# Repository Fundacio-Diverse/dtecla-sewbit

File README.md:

# sew:bit
## Una placa de expansión de código abierto que amplía las posibilidades del micro:bit para la informática textil y los dispositivos wearables en la educación primaria (K-6)
Sew:bit es una placa de expansión de código abierto para el BBC micro:bit, diseñada en el marco de un Fab Lab para facilitar la creación de dispositivos wearables y textiles electrónicos en la educación primaria (de infantil a 6.º de primaria).

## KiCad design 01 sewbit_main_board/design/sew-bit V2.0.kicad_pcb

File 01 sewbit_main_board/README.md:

## Diseño
La placa sew:bit está diseñada usando el EDA open source Kicad en su versión 8.0. En la carpeta Diseño podréis encontrar el editable del mismo, así como el svg de las serigrafía.

Para más información sobre [Kicad](https://www.kicad.org/).

## Producción
La placa se puede fabricar en cualquier casa de fabricación de pcbs, los gerber que hay en la carpeta son los requeridos por JLCPCB en su [guía para exportar archivos de producción en Kicad 8](https://jlcpcb.com/help/article/how-to-generate-gerber-and-drill-files-in-kicad-8).

El edge connector de micro:bit SMD no está disponible, al menos a fecha de Junio 2026, en la lista de partes de JLCPCB y se ha de comprar independientemente, nosotros hemos probado:

- [Sparkfun](https://www.digikey.es/es/products/detail/sparkfun-electronics/17253/13282853)
- [Aliexpress](https://es.aliexpress.com/item/1005008738053304.html?spm=a2g0o.productlist.main.2.45feaLOyaLOy7o&algo_pvid=e5b15cc3-2964-421c-8b64-d8b5d52a2186&algo_exp_id=e5b15cc3-2964-421c-8b64-d8b5d52a2186-1&pdp_ext_f=%7B%22order%22%3A%2218%22%2C%22eval%22%3A%221%22%2C%22fromPage%22%3A%22search%22%7D&pdp_npi=6%40dis%21EUR%211.01%210.88%21%21%211.14%210.99%21%40211b680e17636441302883424e213a%2112000046465521793%21sea%21ES%210%21ABX%211%210%21n_tag%3A-29910%3Bd%3A487d80f5%3Bm03_new_user%3A-29895&curPageLogUid=AhU2Qnlq59mS&utparam-url=scene%3Asearch%7Cquery_from%3A%7Cx_object_id%3A1005008738053304%7C_p_origin_prod%3A)

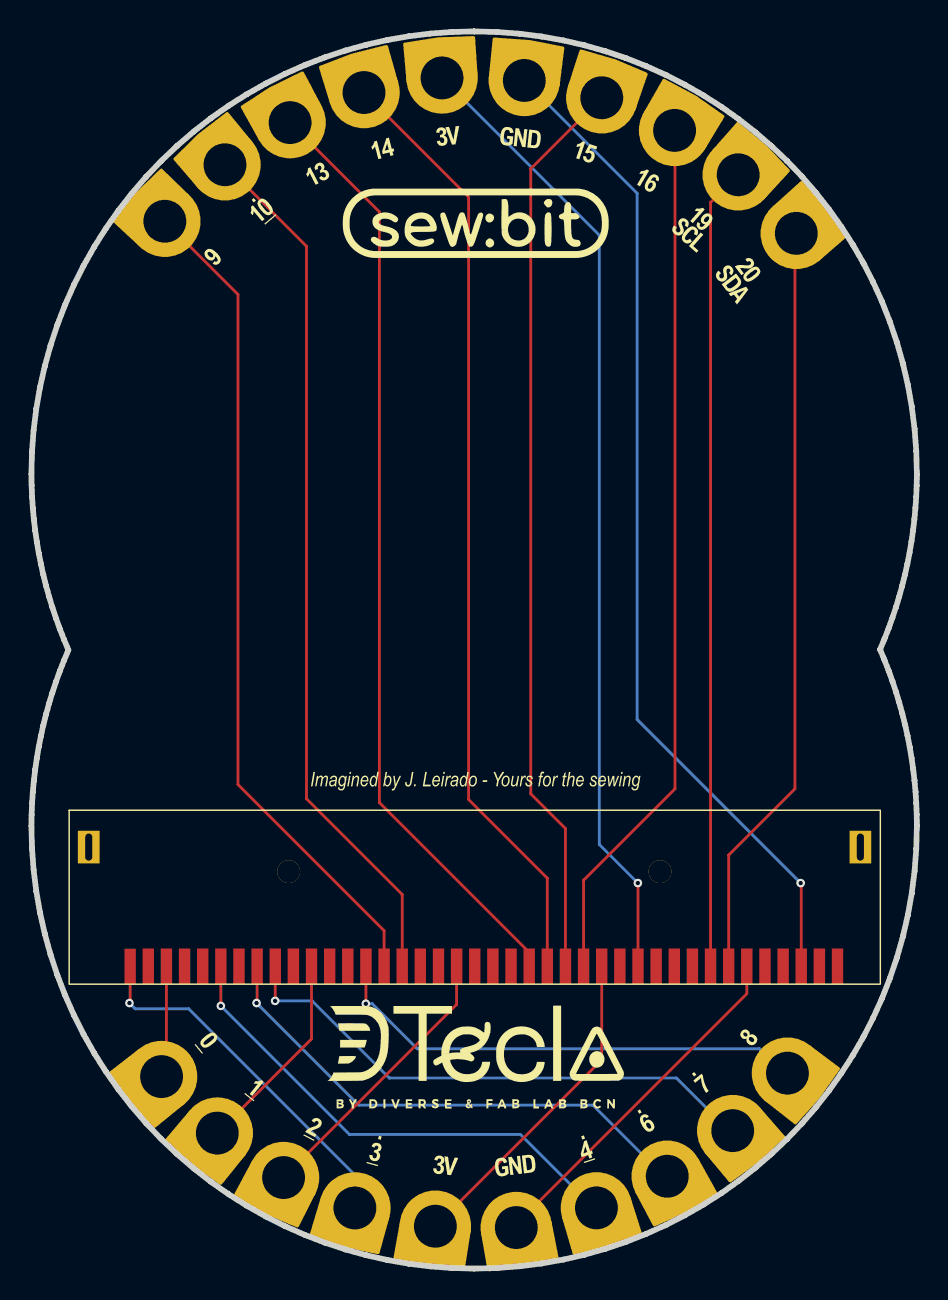
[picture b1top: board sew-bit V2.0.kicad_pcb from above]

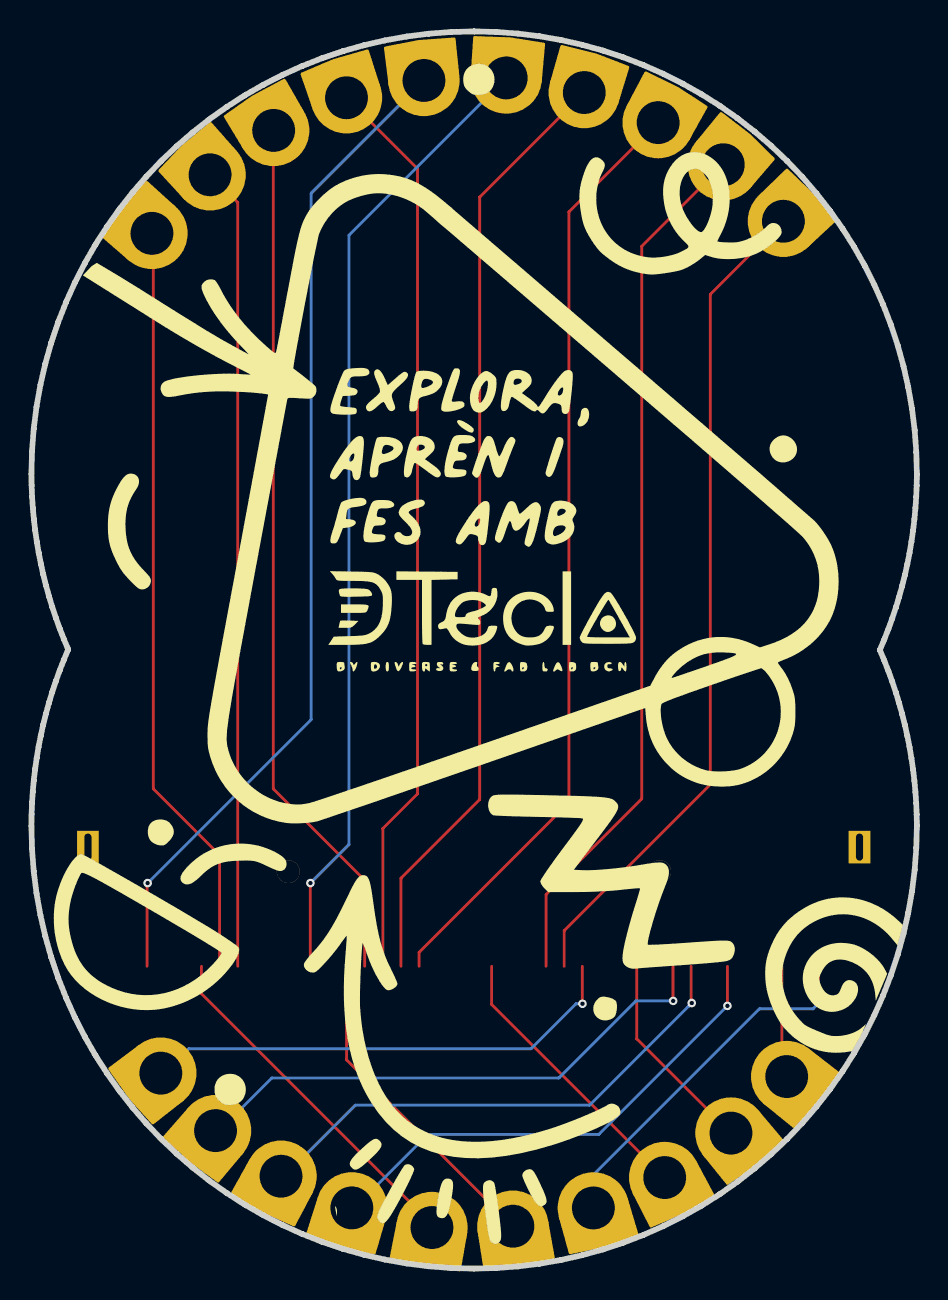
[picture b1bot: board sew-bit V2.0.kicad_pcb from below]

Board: 2 copper layers, 62.0 x 86.6 mm, 5 parts (2 on the bottom side), 18 nets.

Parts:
Micro:bit1: Microbit edge conector 2_SMD
U1, U2, U3, U4: pads x5

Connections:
0: Micro:bit1.2 (P0), Micro:bit1.3 (P0), Micro:bit1.4 (P0), Micro:bit1.5 (P0), U3.1
1: Micro:bit1.10 (P1), Micro:bit1.11 (P1), Micro:bit1.12 (P1), Micro:bit1.13 (P1), U3.2
2: Micro:bit1.19 (P2), Micro:bit1.20 (P2), Micro:bit1.21 (P2), Micro:bit1.22 (P2), U3.3
3: Micro:bit1.1 (P3), U3.4
4: Micro:bit1.6 (P4), U4.4
6: Micro:bit1.8 (P6), U4.3
7: Micro:bit1.9 (P7), U4.2
8: Micro:bit1.14 (P8), U4.1
9: Micro:bit1.15 (P9), U2.5
10: Micro:bit1.16 (P10), U2.4
13: Micro:bit1.23 (P13_SCK), U2.3
14: Micro:bit1.24 (P14_MISO), U2.2
15: Micro:bit1.25 (P15_MOSI), U1.2
16: Micro:bit1.26 (P16), U1.3
19: Micro:bit1.33 (P19_SCL), U1.4
20: Micro:bit1.34 (P20_SDA), U1.5
GND: Micro:bit1.35 (P21_GND), Micro:bit1.36 (GND), Micro:bit1.37 (GND), Micro:bit1.38 (GND), Micro:bit1.39 (GND), Micro:bit1.40 (P22_GND), U1.1, U4.5
VCC: Micro:bit1.27 (P17_3v3), Micro:bit1.28 (3v3), Micro:bit1.29 (3v3), Micro:bit1.30 (3v3), Micro:bit1.31 (3v3), Micro:bit1.32 (P18_3v3), U2.1, U3.5
